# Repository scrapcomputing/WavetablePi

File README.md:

# WavetablePi

WavetablePi is a wavetable module based on the Raspberry Pi Zero 2 W running [mt32-pi](https://github.com/dwhinham/mt32-pi).
It is capable of emulating several midi synthesizers, including mt32, sc55 and general midi with custom sound fonts.
For a complete feature list please refer to the [mt32-pi](https://github.com/dwhinham/mt32-pi) project.

For controlling the mt32-pi from DOS, please use [mt32-pi-control](https://github.com/gmcn42/mt32-pi-control).

- For the "Horizontal" version of this board please check out [WavetablePiHoriz](https://github.com/scrapcomputing/WavetablePiHoriz).

# Features

- It currently supports two modes of audio: using the raspberry pi's PWM audio out (which is noisy and sounds pretty bad), and an external Hi-Fi PCM5102A based DAC.
- You can also attach a 0.91 OLED SSD1306 I2C 128x32 display.
- Starting from rev 0.3 PWM audio is filtered by a simple low-pass filter (R3-C3 and R4-C4).

# I want to build one myself!
- Please note that the current version of the WavetablePi board is quite tall (76mm x 40mm) so please check if it fits your sound card, especially if it needs to be placed perpendicularly to the ISA slots.
- Also please make sure that there is enough clearance between the WavetablePi and the sound card. Some cards have large components that may touch the raspberry pi a
- A WavetablePi with the DAC or the OLED display takes quite a bit of vertical space, so you will end up wasting one ISA slot! There is just no room for a card right next to the sound card, as the OLED display and the DAC will be in the way.
- Finally please check that the PCM5102A HiFi DAC is in the form factor that fits the board. The one I am using is approximately 32mm x 17mm. Also please check that the pinout matches.
- For ordering the PCB, you usually just need to upload the zipped [gerber files](https://github.com/scrapcomputing/WavetablePi/releases/download/rev0.3/WavetablePi_gerbers_rev0.3.zip) to the fab's website.

# Assembly Tips / Troubleshooting
- For attaching the Pi flush against the board, it may be better to cut the 40-pin header into short sections (like 2x3) before soldering them. This should make it easier to solder and to remove the plastic spacers after soldering.
- DAC Board: Before soldering, check if the address solder bridges on the back are set: https://github.com/dwhinham/mt32-pi/wiki/GY-PCM5102-DAC-module
- If the music sounds weird, or slow check `mt32-pi.cfg`. You may need to set `gpio_baud_rate = 31250`.
- Please check out the detailed documentation of the mt32-pi project: https://github.com/dwhinham/mt32-pi

These tips are based on feedback from [ThatRed](https://github.com/ThatRed) (many thanks!). Feel free to check out the full text: https://github.com/scrapcomputing/WavetablePi/issues/1

# Videos
- [Original Wavetable-Pi video](https://www.youtube.com/watch?v=xC-qhcPUeRs)
- [PWM audio improvements](https://www.youtube.com/watch?v=HqzHcLejGF4)
- [Awesome video by Bits und Bolts](https://www.youtube.com/watch?v=s2xgwXyD_c8)

# Bill of materials

For a DigiKey order list with audio-grade parts, DigiKey part numbers and reference designators (for 1 and 10 units), see [bom/README.md](bom/README.md).

Item                                     | #   | Description
-----------------------------------------|-----|-----------------------------------------
Raspberry Pi Zero 2 W                    | 1   | The older RPi Zero is not fast enough
40-pin 2x20 male header 2.54mm pitch     | 1   | For attaching the RPi to the board.
26-pin 2x13 female header 2.54mm pitch   | 1   | For attaching the board to the wavetable header
6-pin 2x3 pin male header 2.54mm pitch   | 1   | For the audio select jumpers
Jumper 2.54mm pitch                      | 2   | Jumpers for the audio selection header
Capacitor 10uF through-hole ceramic      | 2   |
Capacitor 100nF through-hole ceramic     | 2   | C3 and C4 which form the PWM audio low-pass filter along with R3 and R4. 100nF is for a 1.6KHz cutoff frequency. Use lower values for higher cutoff
Resistor 22K Ohm                         | 1   |
Resistor 10K Ohm                         | 1   |
Resistor 1K Ohm                          | 2   | R3 and R4, which along with C3 and C4 form a low-pass filter of the PWM audio
0.91 OLED SSD1306 I2C 128x32 module      | 1   | (Optional)
PCM5102A I2S DAC Module (aka GY PCM5120) | 1   | (Optional but highly recommended) Please check the PCB for the supported dimensions and form factor!

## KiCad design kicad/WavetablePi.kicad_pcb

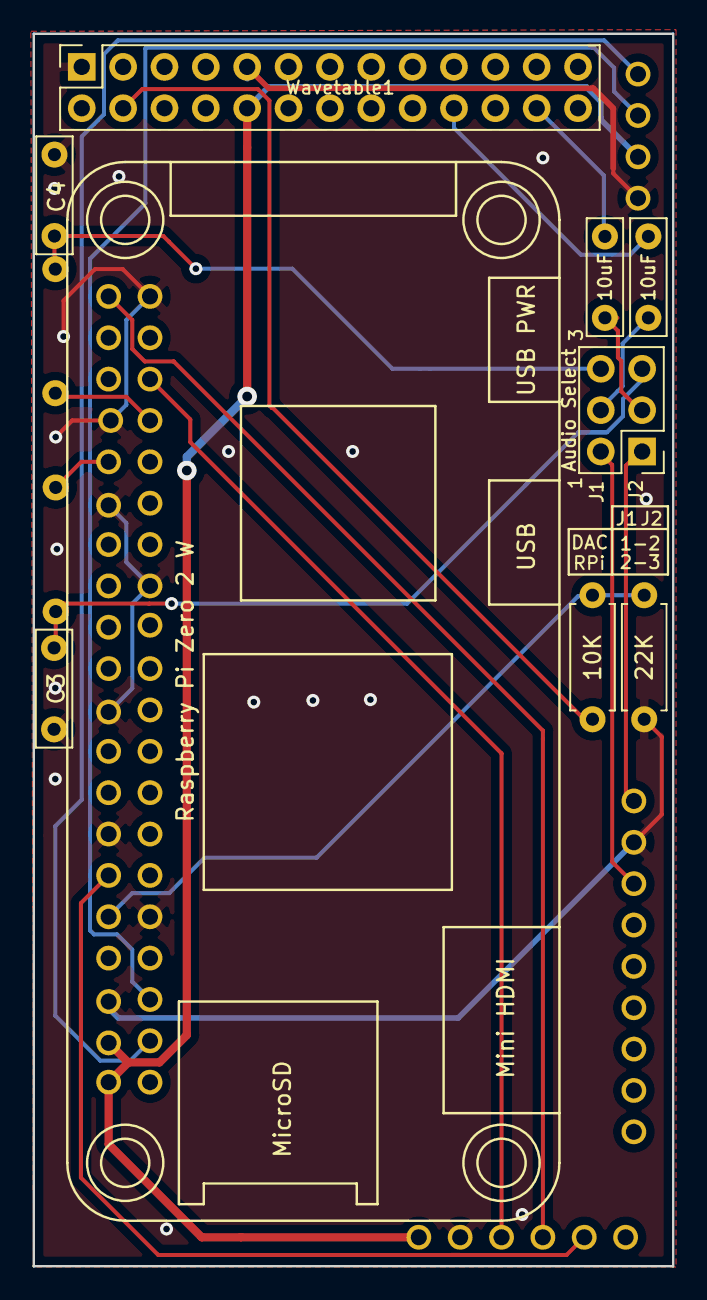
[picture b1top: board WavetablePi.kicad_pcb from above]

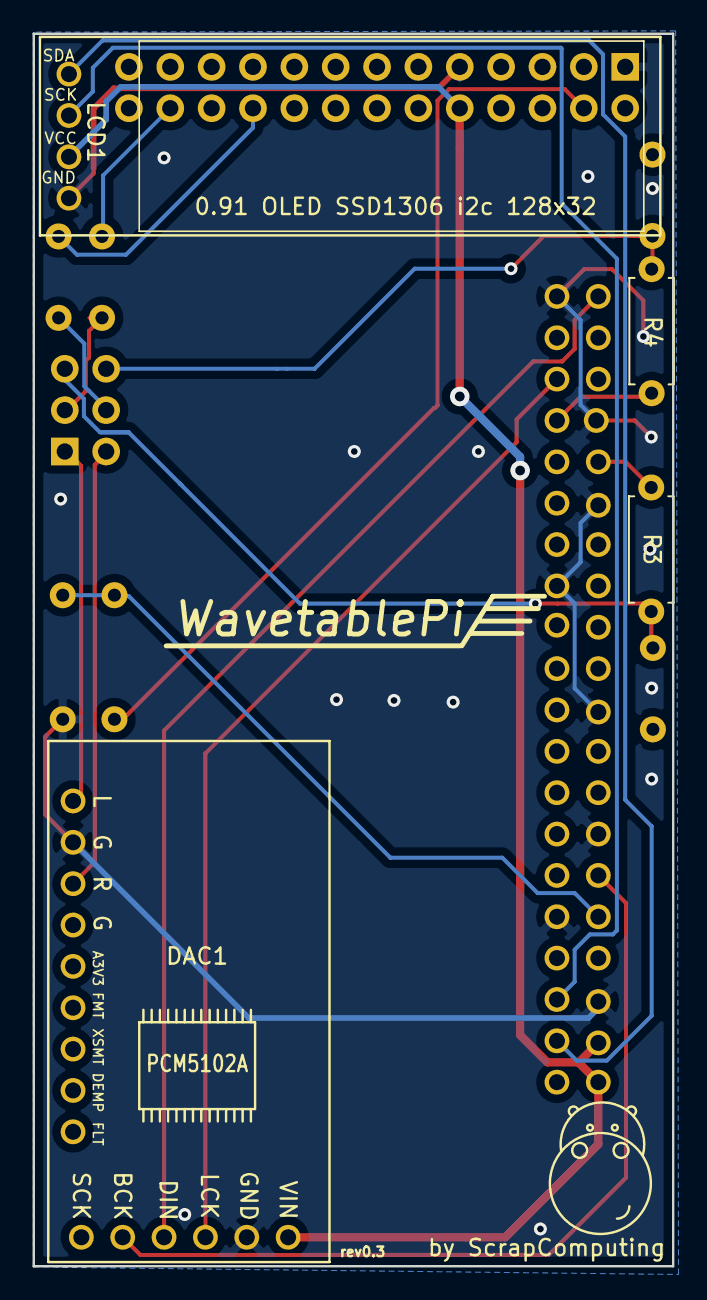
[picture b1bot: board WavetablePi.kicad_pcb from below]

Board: 2 copper layers, 39.3 x 75.7 mm, 13 parts (4 on the bottom side), 19 nets.

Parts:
10K: 10K; R_Axial_DIN0207_L6.3mm_D2.5mm_P7.62mm_Horizontal
10uF, 10uF#2: 10uF; C_Rect_L7.0mm_W2.0mm_P5.00mm
22K: 22K; R_Axial_DIN0207_L6.3mm_D2.5mm_P7.62mm_Horizontal
Audio Select: Conn_02x03_Odd_Even; PinHeader_2x03_P2.54mm_Vertical
C3: 100nF; C_Rect_L7.0mm_W2.0mm_P5.00mm
C4: C; C_Rect_L7.0mm_W2.0mm_P5.00mm
DAC1: GY_PCM5102A
LCD1: LCD_0.91_OLED
R3, R4: 1K; R_Axial_DIN0207_L6.3mm_D2.5mm_P7.62mm_Horizontal
Raspberry Pi Zero 2 W: RPiZero2W
Wavetable1: Conn_02x13_Odd_Even; PinSocket_2x13_P2.54mm_Vertical

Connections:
+5V: DAC1.6, LCD1.3, Raspberry Pi Zero 2 W.2, Raspberry Pi Zero 2 W.4, Wavetable1.10
GND: 22K.2, C3.2, C4.2, DAC1.5, DAC1.14, LCD1.4, Raspberry Pi Zero 2 W.6, Raspberry Pi Zero 2 W.9, Raspberry Pi Zero 2 W.14, Raspberry Pi Zero 2 W.20, Raspberry Pi Zero 2 W.25, Raspberry Pi Zero 2 W.30, Raspberry Pi Zero 2 W.34, Raspberry Pi Zero 2 W.39, Wavetable1.1, Wavetable1.9
unnamed: Audio Select.1, DAC1.15
unnamed: Audio Select.2, DAC1.13
unnamed: 10uF.2, Audio Select.3
unnamed: 10uF#2.2, Audio Select.4
unnamed: Audio Select.5, C3.1, R3.1
unnamed: Audio Select.6, C4.1, R4.1
unnamed: 10uF.1, Wavetable1.24
unnamed: 10uF#2.1, Wavetable1.20
unnamed: DAC1.2, Raspberry Pi Zero 2 W.12
unnamed: DAC1.3, Raspberry Pi Zero 2 W.40
unnamed: DAC1.4, Raspberry Pi Zero 2 W.35
unnamed: LCD1.1, Raspberry Pi Zero 2 W.3
unnamed: LCD1.2, Raspberry Pi Zero 2 W.5
unnamed: 10K.1, 22K.1, Raspberry Pi Zero 2 W.10
unnamed: 10K.2, Wavetable1.4
unnamed: R3.2, Raspberry Pi Zero 2 W.32
unnamed: R4.2, Raspberry Pi Zero 2 W.33

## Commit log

2023-01-16 Initial commit rev0.2
2023-01-23 Adds a low-pass filter for PWM audio
    Improves the audio quality of PWM audio with a simple low-pass filter.
    This uses R3-C3 and R4-C4 (one filter for each channel).
2023-01-23 Updated link to gerbers
2023-05-20 Readme: Add tips and video links
2023-10-21 Add schematic image
2024-06-11 README update
2025-03-17 README: updated video links
